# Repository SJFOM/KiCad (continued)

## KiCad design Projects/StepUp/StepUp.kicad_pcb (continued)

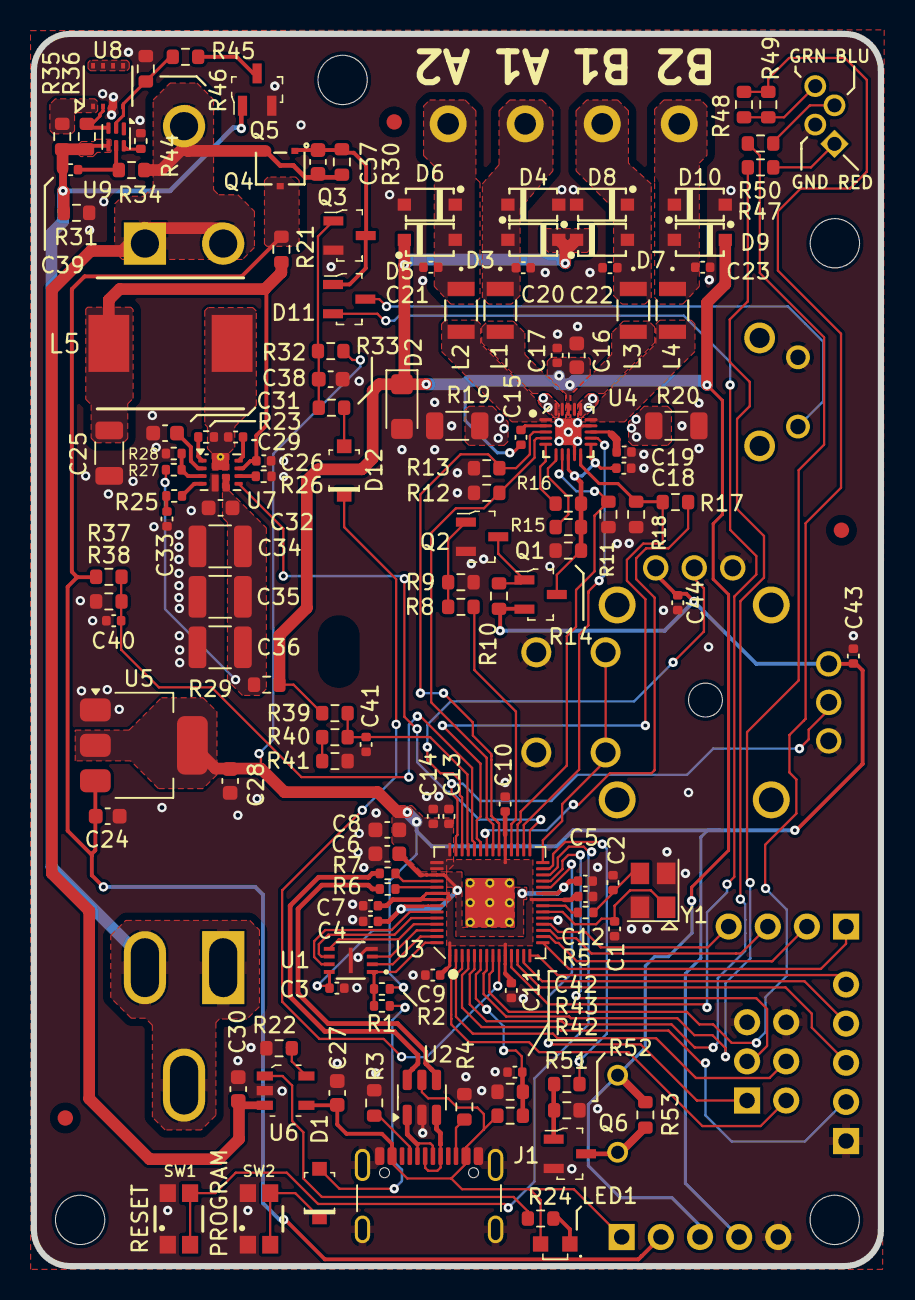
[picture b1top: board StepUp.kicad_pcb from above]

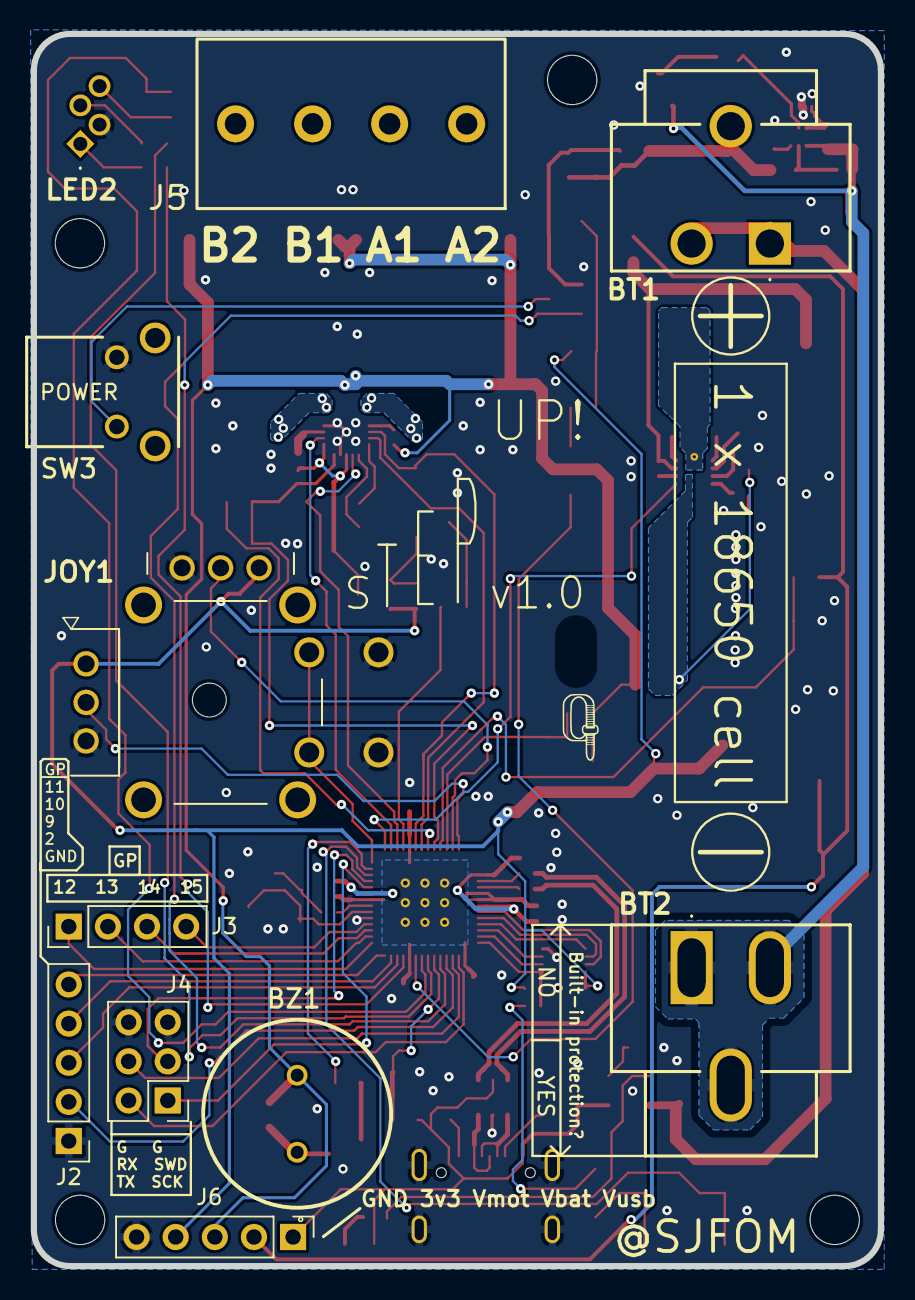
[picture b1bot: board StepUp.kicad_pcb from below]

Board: 4 copper layers, 55.0 x 80.0 mm, 155 parts (12 on the bottom side), 107 nets.

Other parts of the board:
LOGO1: Zip-tie; LOGO

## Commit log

2024-01-21 feat(kicad): First push of local files
2024-01-21 chore(sub): Fixing digikey submodule
2024-01-21 feat(sub): New submodule entry
2024-01-21 feat(setup): KiCad symbolic link setup
2024-03-11 feat(v8): Update to KiCAD v8, added boost converter
2024-03-16 feat(rp2040): Layout begins, extra libraries
    RPico minimal project downloaded + assets copied. Boost converter layout
    in progress, 18650 battery holder added.
2024-03-17 feat(joystick): Added part
2024-03-19 feat(charge): Charge IC, USB ESD, sheet sections
2024-03-20 feat(power): Input stage updates
    USB vs Vbat source selection using PMOS gate logic.
2024-04-25 feat(stepup): Many additions
2024-04-27 feat(stepup): Schematic + PCB updates
2024-04-28 feat(schematic): Ready for layout
2024-04-29 chore(pins): MCU_BOOST_EN to MCU, fixed errors
2024-04-29 test(yml): Generate kicad files
2024-04-29 test(yml): Test project path
2024-04-29 test(yml): Test
2024-05-06 feat(layout): Blocks organised
2024-05-07 feat(tidy): Bigger PMOS, added footprints
2024-05-12 feat(layout): TMC & Boost layout begin
2024-05-27 feat(layout): DRC ongoing, layout nearly complete
2024-05-30 feat(StepUp): Release v0.1
2024-05-30 feat(outputs): Added STEP file & schematic output
2024-06-02 feat(BoM): Updating PN's
2024-06-04 chore(bom): Update from PCB BoM
2024-06-17 chore(d12): Update diode silkscreen
2024-10-28 feat(v0.2): Schematic updated, PCB layout start
2024-10-28 feat(v0.2): Rough layout begins
2024-11-17 feat(cad): CAD dims pushed to PCB
2024-11-24 feat(v0.2): Component layout from CAD
2024-11-25 feat(layout): Layout begins
2024-11-27 feat(layout): Most traces complete
2024-12-07 feat(v0.2): Release, PCBs ordered!
2025-02-22 feat(v0.3): Begin work on next rev
2025-02-22 feat(v0.3): Boost layout complete
2025-02-23 feat(v0.3): Layout 90% complete
2025-02-27 feat(v0.3): Files sent to PCBWay for build
2025-03-03 feat(v0.3): Minor updates for PCBWay order
2025-03-03 chore(date): Update date for sch & PCB
2026-03-26 chore(3d): 3D model file path update
2026-03-27 feat(v0.4): Work in Progress
2026-03-27 chore(yml): Run tests against v9 (not v8)
2026-03-30 chore(unused): Remove unused files/folders
2026-03-30 feat(v1.0): Migrate v0.4 to v1.0
